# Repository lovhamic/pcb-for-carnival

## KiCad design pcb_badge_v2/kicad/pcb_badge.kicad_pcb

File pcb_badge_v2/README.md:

# Space Carnival PCB Badge v2 - Echoes of Years

40 x 40 mm, 2-layer. 8 x 3 mm LEDs on the Ferris-wheel joints (top, UL, UR, L, R, hub, LL, LR; bottom joint hidden by the tent is skipped).
One shared 68R resistor, CR2032 + through-hole holder on the back.
Folders: kicad/, gerbers/ (+drill), schematic/, bom/, render/, scripts/.
Fab: 2 layers, 1.6 mm, white mask, black silkscreen (the silk is the artwork).
Verify before ordering: holder footprint vs the real part, LED (D8) joints vs holder body, silk fine detail in the fab preview.

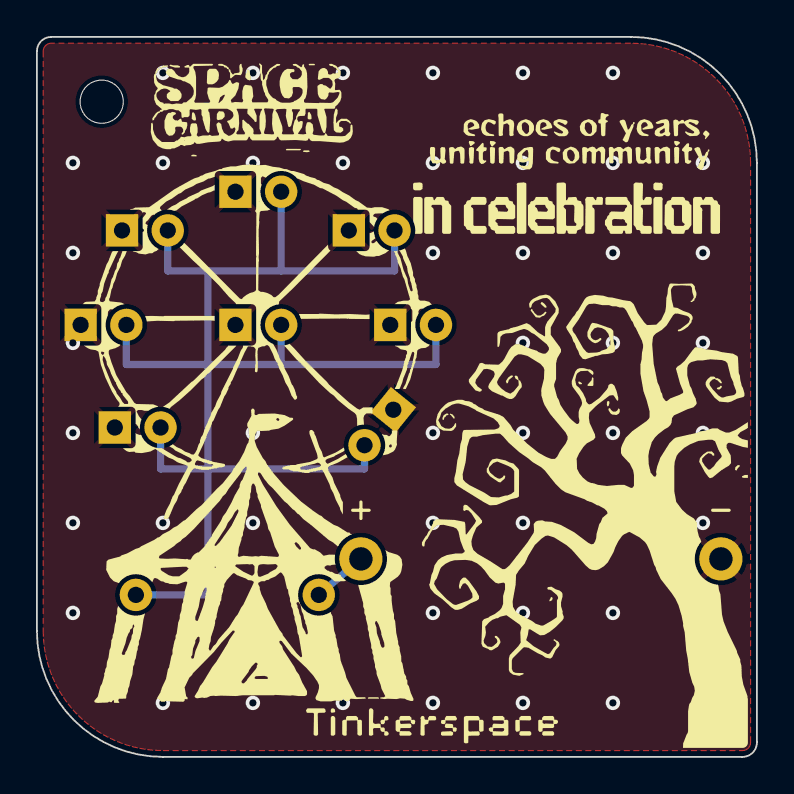
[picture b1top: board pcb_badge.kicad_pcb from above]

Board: 2 copper layers, 40.0 x 40.0 mm, 11 parts (1 on the bottom side), 3 nets.

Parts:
BT1: CR2032 holder; CR2032_Holder_THT_20mm
D1, D2, D3, D4, D5, D6, D7, D8: LED_D3.0mm; LED_D3.0mm_Pitch2.54mm
H1: Lanyard; LanyardHole_2.4mm
R1: 68R; R_Axial_P10.16mm

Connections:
GND: BT1.2, D1.1, D2.1, D3.1, D4.1, D5.1, D6.1, D7.1, D8.1
VBAT: BT1.1, R1.2
VLED: D1.2, D2.2, D3.2, D4.2, D5.2, D6.2, D7.2, D8.2, R1.1

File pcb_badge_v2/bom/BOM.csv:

Comment,Designator,Footprint,Qty,LCSC Part #,Notes
"LED 3mm through-hole, red or amber (Vf ~2.0 V)","D1,D2,D3,D4,D5,D6,D7,D8","LED_D3.0mm, 2.54 mm pitch",8,,"Flat side / short lead = cathode = square pad, on the LEFT of each LED (front view); D8 (lower-right) is rotated. No white/blue: Vf ~3 V is too high for a coin cell."
"68R 1/4W axial resistor, through-hole","R1","R_Axial 10.16 mm pitch",1,,"One shared resistor for all 8 LEDs. Tune 47-100R for brightness vs battery life."
"CR2032 coin cell holder, through-hole, 2-pin","BT1","CR2032_Holder_THT_20mm",1,,"Mounted on the BACK, pins soldered from the front. Footprint assumes 20.0 mm pin pitch / 1.3 mm drill - verify against your holder."
"CR2032 3V coin cell","(battery)","-",1,,"Not on the PCB netlist"
